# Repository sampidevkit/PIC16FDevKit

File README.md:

# PIC16F877A MICROCONTROLLER DEVELOPMENT KIT

## 1. Sơ Đồ Khối

## 2. Sơ Đồ Nguyên Lý

## 3. Vi Điều Khiển Chính PIC16F877A

## 4. Môi Trường Lập Trình, Trình Biên Dịch và Công Cụ Hỗ Trợ

### 4.1. Môi Trường Lập Trình MPLAB X IDE

### 4.2. Trình Biên Dịch MPLAB XC8

## 5. Mạch Nạp Tích Hợp

### 5.1. Nạp Chương Trình Mạch Nạp

### 5.2. Cập Nhật Chương Trình Mạch Nạp

### 5.3 Các Trạng Thái LED Lỗi

## 6. Hướng Dẫn Lập Trình Cơ Bản

## 7. Tài Liệu Kỹ Thuật:
* [PIC16F87XA Datasheet](https://ww1.microchip.com/downloads/aemDocuments/documents/MCU08/ProductDocuments/DataSheets/39582C.pdf).
* [PIC16F87XA Programming Specifications](https://ww1.microchip.com/downloads/en/DeviceDoc/39589C.pdf).

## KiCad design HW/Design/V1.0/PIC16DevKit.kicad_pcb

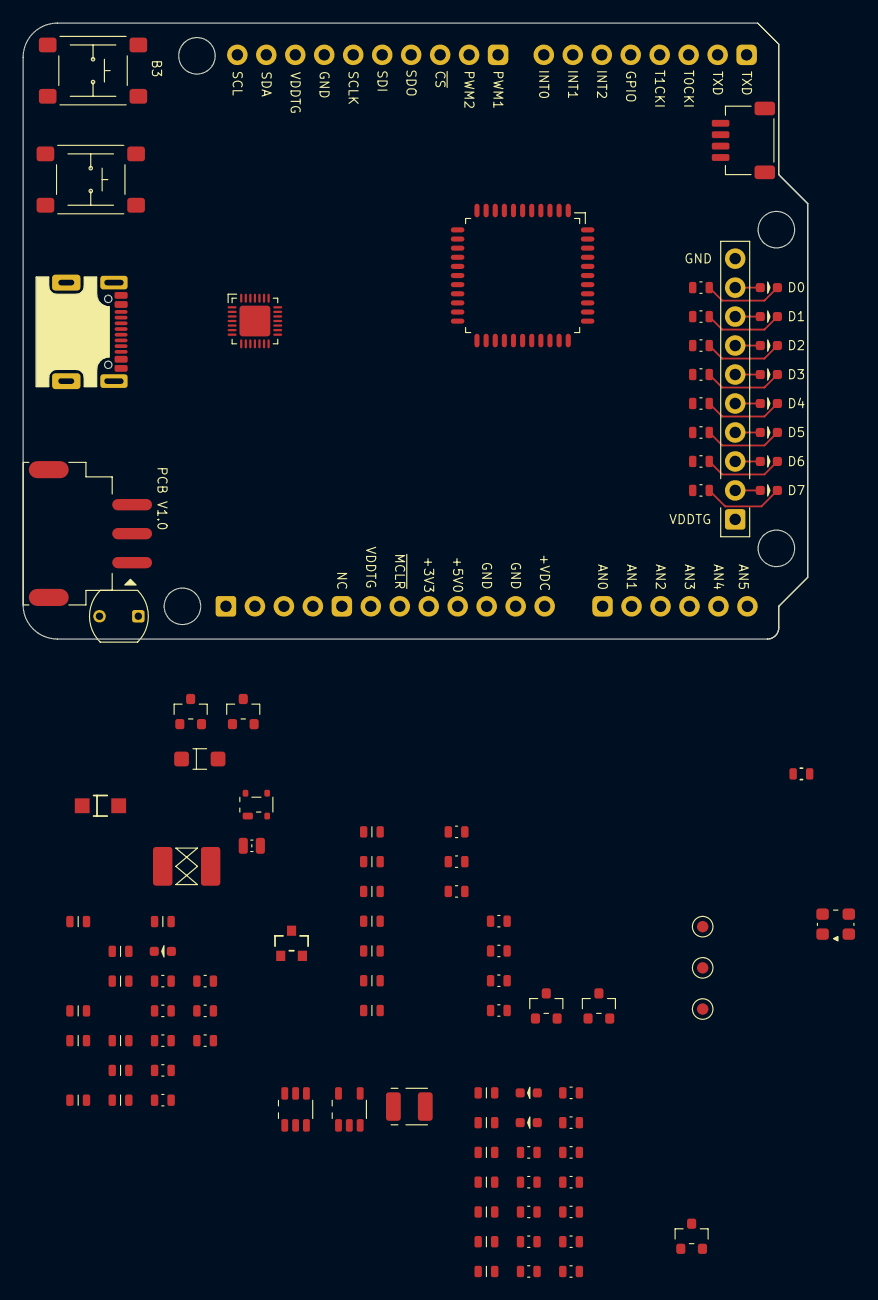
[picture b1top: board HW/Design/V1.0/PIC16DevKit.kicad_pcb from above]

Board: 4 copper layers, 68.8 x 54.0 mm, 99 parts (0 on the bottom side), 84 nets.

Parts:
BT301: FNC; SW6x6-G
BT401: UBT; SW6x6-G
C202, C207, C209, C211, C212, C218, C307, C404: 10uF; CAP0603
C205, C214, C402, C403: 22pF; CAP0603
C215, C216, C301, C302, C303, C304, C305, C401, C405, C406, C407: 100nF; CAP0603
C217: 220uF; CAP1411
C306: 470nF; CAP0603
D201: TVS 5V; SOT143B_NEXT
D202, D204: 200mA/0.2VF; SOD-123FL
D205: POWER; LED0603
D301: TGRD; LED0603
D302: BUSY; LED0603
D401: D7; LED0603
D402: D6; LED0603
D403: D5; LED0603
D404: D4; LED0603
D405: D3; LED0603
D406: D2; LED0603
D407: D1; LED0603
D408: D0; LED0603
F202: 500mA; FUSE1812
J201: USB C; USB4105
J401: EXP PORT; HDM1x10x2.54_TH
J402: QWIIC; HDM-1x4x1.0-RA
J403: For DS18B20; JST-XH2.54-3P-SMD-RA
L201: 10uH/100mA; IND0805
MD401: ARDUINO-UNO-R3
Q201, Q202: SI2301; SOT23
Q203: 2N3906; SOT23
Q301, Q401, Q402: SI2302; SOT23
R201, R202, R413, R414, R415, R416, R417: 5.1K; RES0603
R203, R204, R205: 100K; RES0603
R208: 191K; RES0603
R209, R303, R305, R401, R403: 10K; RES0603
R210, R405, R406, R407, R408, R409, R410, R411, R412: 1K; RES0603
R301, R302, R304, R306, R307, R308, R309, R310, R311, R312, R404: 330R; RES0603
R402: 10K; CDS-5MM
TP401: PGM/B3; TP1MM
TP402: PGC/B6; TP1MM
TP403: PGD/B7; TP1MM
U202: BOOST 12V; SOT-23-6_MCHP
U203: LDO 3.3V/300mA; SOT-23-5_MCHP
U301: AVRxxDU28; VQFN28-4x4-EP
U401: 20MHz; CDFN3225-4LD-PL-1
U402: PIC16F877A; TQFP44-10x10-P0.8

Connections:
+3.3V: C218.2, J402.2 (VDD), MD401.4 (+3V3), Q401.1 (G), Q402.1 (G), R415.2, R416.2, U203.5 (VOUT)
+5V: C205.1, C207.2, C215.1, C217.+, C304.1, C305.1, C307.1, L201.1, MD401.5 (+5V), MD401.P2 (+5V), Q201.2 (S), Q202.2 (S), Q203.2 (E), R205.1, R210.2, R303.2, R305.2, U202.5 (IN), U301.18 (VDD), U301.24 (VDD)
+VDDTG: C209.2, C211.2, C406.1, C407.1, J401.1, MD401.2 (IOREF), MD401.30 (AREF), Q202.3 (D), R403.1, R404.1, R413.2, R414.2, R417.2, U203.1 (VIN), U402.7 (VDD), U402.28 (VDD)
/POWER/USB_N: D201.3 (CH2), J201.A7 (DN1), J201.B7 (DN2), U301.7 (DM)
/POWER/USB_P: D201.2 (CH1), J201.A6 (DP1), J201.B6 (DP2), U301.8 (DP)
/POWER/V33_EN: U203.3 (EN), U301.12 (PD2/ACINP/AIN9)
/POWER/VPP_EN: U202.4 (EN), U301.21 (PF1/ANI16/XTAL32K2)
/POWER/~VTG_EN: C205.2, Q202.1 (G), R205.2, U301.20 (PF0/AIN15/XTAL32K1)
/PROGRAMMER/RXD0: R309.2, U402.1 (DT/RX/RC7), U402.44 (CK/TX/RC6)
/PROGRAMMER/RXD1: MD401.15 (D0/RXD), R310.2
/PROGRAMMER/SCL: MD401.32 (D15/SCL), Q401.3 (D), R308.2, R413.1, TP402.1, U301.1 (PA3/A1RX0/SCL/AIN1), U402.16 (PGC/RB6)
/PROGRAMMER/SDA: MD401.31 (D14/SDA), Q402.3 (D), R306.2, R414.1, TP403.1, U301.28 (PA2/A1TX0/SDA/AIN0), U402.17 (PGD/RB7)
/PROGRAMMER/TXD1: MD401.16 (D1/TXD), R312.2
/PROGRAMMER/UPDI: MD401.P4 (UPDI), U301.23 (PF7/UPDI)
/PROGRAMMER/~RESET: C303.2, MD401.P1 (~RESET), R305.1, U301.22 (PF6/~RESET)
/PROGRAMMER/~TG_MCLR: C302.1, MD401.3 (~MCLR), Q301.3 (D), R304.1, U402.18 (~MCLR/VPP)
/PROGRAMMER/~TG_PGM: BT401.1, BT401.2, C405.1, R307.2, R403.2, TP401.1, U402.11 (PGM/RB3)
AN0: MD401.9 (AN0), U402.19 (AN0/RA0)
AN1: MD401.10 (AN1), U402.20 (AN1/RA1)
AN2: MD401.11 (AN2), U402.21 (CVREF/VREF-/AN2/RA2)
AN3: MD401.12 (AN3), U402.22 (VREF+/AN3/RA3)
AN4: MD401.13 (AN4/SDA), U402.24 (~SS/C2OUT/AN4/RA5)
AN5: MD401.14 (AN5/SCL), U402.25 (RE0/~RD/AN5)
GND: BT301.3, BT301.4, BT401.3, BT401.4, C202.1, C207.1, C209.1, C211.1, C212.2, C215.2, C216.2, C217.-, C218.1, C301.2, C302.2, C303.1, C304.2, C305.2, C306.2, C307.2, C401.2, C402.1, C403.2, C404.1, C405.2, C406.2, C407.2, D201.1 (GND), D205.K, D301.K, D302.K, J201.A1B12 (GND), J201.B1A12 (GND), J201.S1, J201.S2, J201.S3, J201.S4, J401.10, J402.0 (EP), J402.1 (GND), J403.0 (EP), J403.1 (GND), MD401.6 (GND), MD401.7 (GND), MD401.29 (GND), MD401.P3 (GND), Q301.2 (S), R201.2, R202.1, R203.2, R204.2, R209.2, R401.2, R405.1, R406.1, R407.1, R408.1, R409.1, R410.1, R411.1, R412.1, U202.2 (GND), U203.2 (GND), U301.19 (GND), U301.25 (GND), U301.29 (EP), U401.2 (GND1), U401.4 (X2), U402.6 (VSS), U402.29 (VSS)
GPIO: MD401.19 (D4), U402.15 (RB5)
INT0: MD401.22 (D7), U402.8 (INT/RB0)
INT1: MD401.21 (D6), U402.9 (RB1)
INT2: MD401.20 (D5), U402.10 (RB2)
LED_BUSY: R302.2, U301.3 (PA5/MISO/A2RX0/AIN3)
LED_TGRDY: R301.2, U301.2 (PA4/MOSI/A2TX0/AIN2)
LIGHT: C401.1, R401.1, R402.1, U402.27 (RE2/~CS/AN7)
unnamed: D201.4 (CH3), F202.1, J201.A4B9 (VBUS), J201.B4A9 (VBUS)
unnamed: D205.A, R210.1
unnamed: D301.A, R301.1
unnamed: D302.A, R302.1
unnamed: D401.K, R405.2
unnamed: D402.K, R406.2
unnamed: D403.K, R407.2
unnamed: D404.K, R408.2
unnamed: D405.K, R409.2
unnamed: D406.K, R410.2
unnamed: D407.K, R411.2
unnamed: D408.K, R412.2
unnamed: J201.A5 (CC1), R202.2
unnamed: J201.B5 (CC2), R201.1
unnamed: J402.4 (SCL), Q401.2 (S), R415.1
unnamed: J402.3 (SDA), Q402.2 (S), R416.1
unnamed: C404.2, J403.3 (VDD), R402.2, R404.2
unnamed: Q201.1 (G), Q203.3 (C), R204.1
unnamed: D202.K, Q203.1 (B), R203.1
unnamed: C214.2, R208.2, R209.1, U202.3 (FB)
unnamed: D204.A, L201.2, U202.1 (SW)
unnamed: C216.1, U203.4 (NC/BP)
unnamed: R308.1, U301.26 (PA0/TX0/ASDA/XTALHF1)
unnamed: R306.1, U301.27 (PA1/RX0/ASCL/XTALHF2)
unnamed: R307.1, U301.4 (PA6/SCLK/AIN4)
unnamed: R311.1, U301.14 (PD4/AMOSI/A3TX0/AIN11)
unnamed: R309.1, U301.15 (PD5/AMISO/A3RX0/AIN12)
unnamed: R312.1, U301.16 (PD6/ASCLK/TX1/ACINP/AIN13)
unnamed: R310.1, U301.17 (PD7/RX1/AINN/AIN14)
unnamed: C306.1, U301.6 (VUSB)
unnamed: C403.1, U401.3 (GND2), U402.30 (OSC1/CLKI)
unnamed: C402.2, U401.1 (X1), U402.31 (OSC2/CLKO)
ONE_WIRE: J403.2 (DQ), R417.1, U402.26 (RE1/~WR/AN6)
PWM1: MD401.23 (D8), U402.36 (CCP1/RC2)
PWM2: MD401.24 (D9), U402.35 (T1OSI/CCP2/RC1)
RD0: D408.A, J401.9, U402.5 (RD7/PSP7)
RD1: D407.A, J401.8, U402.4 (RD6/PSP6)
RD2: D406.A, J401.7, U402.3 (RD5/PSP5)
RD3: D405.A, J401.6, U402.2 (RD4/PSP4)
RD4: D404.A, J401.5, U402.41 (RD3/PSP3)
RD5: D403.A, J401.4, U402.40 (RD2/PSP2)
RD6: D402.A, J401.3, U402.39 (RD1/PSP1)
RD7: D401.A, J401.2, U402.38 (RD0/PSP0)
SCLK: MD401.28 (D13/SCLK), U402.37 (SCK/SCL/RC3)
SDI: MD401.27 (D12/MISO), U402.42 (SDI/SDA/RC4)
SDO: MD401.26 (D11/MOSI), U402.43 (SDO/RC5)
T0CKI: MD401.17 (D2), U402.23 (C1OUT/T0CKI/RA4)
T1CKI: MD401.18 (D3), U402.32 (T1OSO/T1CKI/RC0)
TG_MCLR: Q301.1 (G), U301.13 (PD3/ACINN/AIN10)
VBUS: C202.2, D202.A, F202.2, Q201.3 (D)
VPP: C212.1, C214.1, D204.K, R208.1, R304.2
~BT_FNC: BT301.1, BT301.2, C301.1, R303.1, U301.5 (PA7/ACOUT/AIN5)
~CS: MD401.25 (D10/~SS), U402.14 (RB4)

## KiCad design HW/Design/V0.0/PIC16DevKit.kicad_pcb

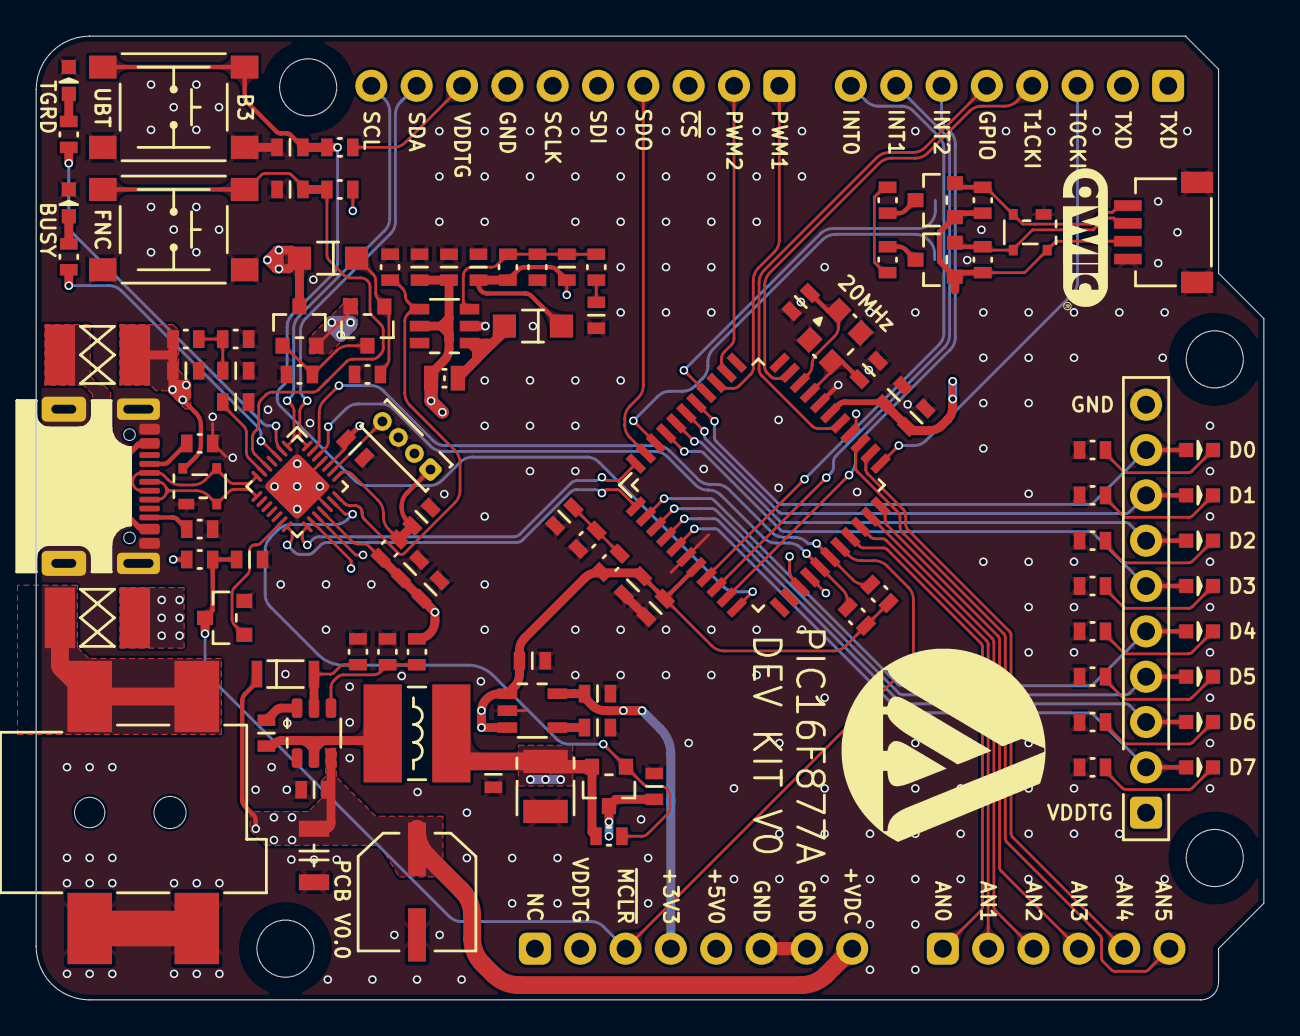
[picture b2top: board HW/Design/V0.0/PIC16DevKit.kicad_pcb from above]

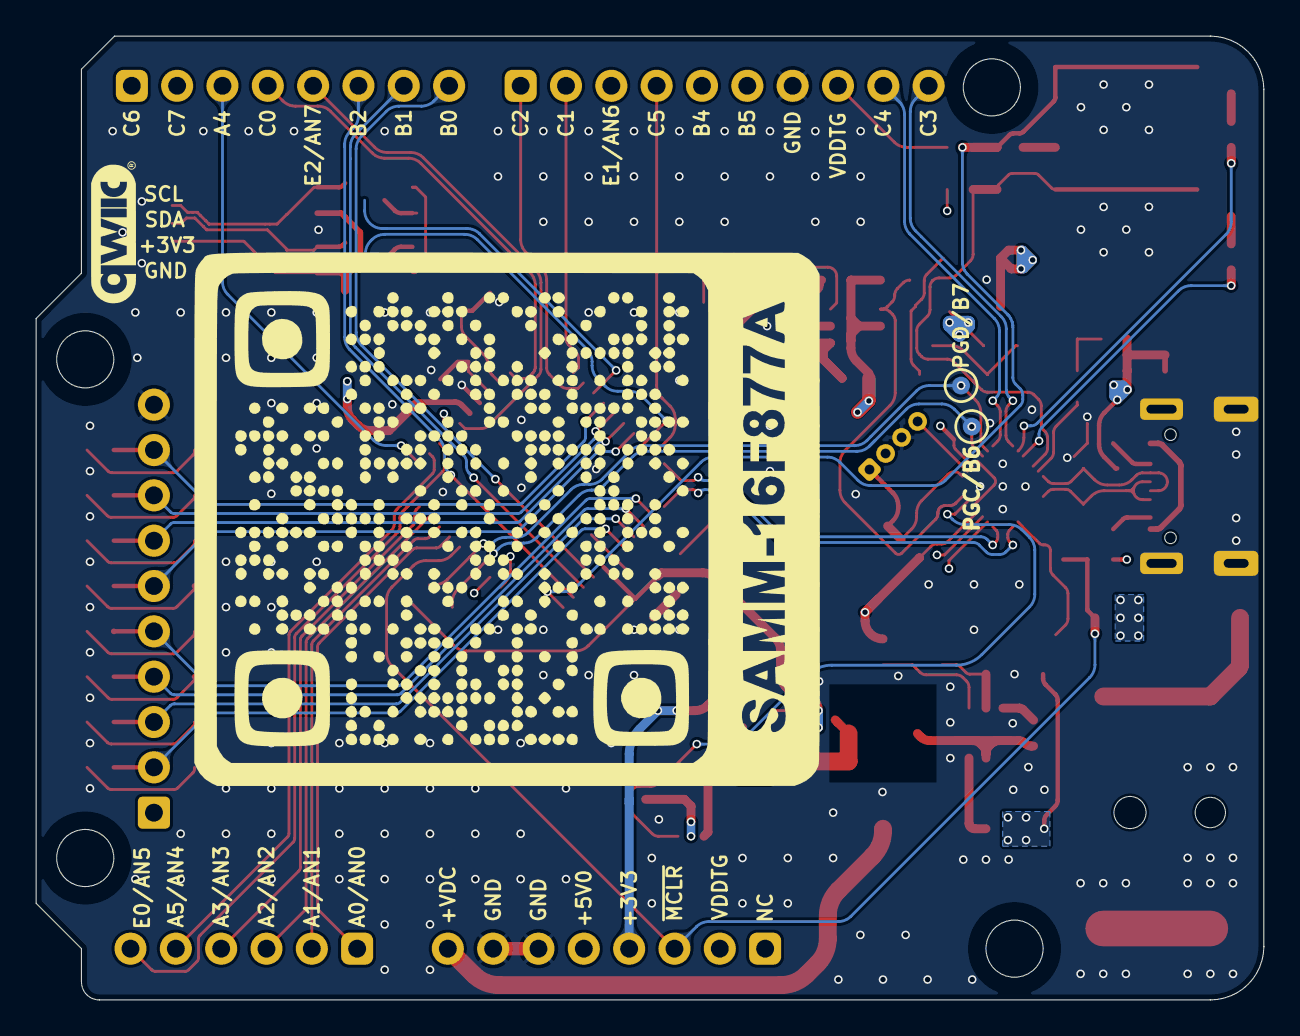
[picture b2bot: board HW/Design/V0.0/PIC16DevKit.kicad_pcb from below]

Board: 4 copper layers, 68.8 x 54.0 mm, 109 parts (2 on the bottom side), 84 nets.

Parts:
BT1: FNC; SW6x6-G
BT2: UBT; SW6x6-G
C1: 220uF; CAP_ELEC-6.6x6.6-DIA6.3
C2: 220uF; CAP1411
C3: 10uF/16V; CAP1206
C4, C5, C6, C14, C17, C18, C20, C22, C25, C26, C32, C37, C38, C39, C40, C41: 100nF; CAP0603
C7, C8, C9, C10, C11, C13, C19, C21, C27: 10uF; CAP0603
C12, C15, C16: 22pF; CAP0603
C23: 470nF; CAP0603
D1: 5V1; SOD80C-LL34
D2, D4: 200mA/0.2VF; SOD-123FL
D3, D5: TVS 5V; SOT143B_NEXT
D6: TGRD; LED0603
D7: BUSY; LED0603
D8: D0; LED0603
D9: D1; LED0603
D10: D2; LED0603
D11: D3; LED0603
D12: D4; LED0603
D13: D5; LED0603
D14: D6; LED0603
D15: D7; LED0603
F1: 1A; FUSE1812
F2: 500mA; FUSE1812
J1: 9V-12V; PJ-002AH-SMT
J2: USB C; USB4105
J3: EXP PORT; HDM1x10x2.54_TH
J4: SIL04; HD-1x4x1.27MM-TH
J5: QWIIC; HDM-1x4x1.0-RA
L1: 10uH/1.4A; IND5852
L2: 10uH/100mA; IND0805
MD1: ARDUINO-UNO-R3
Q1, Q3: SI2301; SOT23
Q4: 2N3906; SOT23
Q5, Q6, Q7: SI2302; SOT23
R1: 52.3K, 1%; RES0603
R2, R10, R36: 10K, 1%; RES0603
R3, R8, R9, R31: 100K; RES0603
R4, R18, R23, R26: 10K; RES0603
R5: 191K, 1%; RES0603
R6, R7, R19, R21, R22, R27, R28, R30, R32, R35: 5.1K, 1%; RES0603
R11, R12, R13, R14, R15, R16, R17, R20, R24, R25, R29: 330R; RES0603
R33, R34: 47K, 1%; RES0603
TP1: PGC/B6; TP1MM
TP2: PGD/B7; TP1MM
U1: LDO 3.3V/300mA; SOT-23-5_MCHP
U2: MT1470; SOT-23-6_MCHP
U3: MT3608; SOT-23-6_MCHP
U4: PIC16F877A; TQFP44-10x10-P0.8
U5: AVRxxDU28; VQFN28-4x4-EP
U10: 20MHz; CDFN3225-4LD-PL-1

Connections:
+3.3V: C8.1, D5.4 (CH3), J5.2 (VDD), MD1.4 (+3V3), Q6.1 (G), Q7.1 (G), R28.1, R30.1, U1.5 (VOUT)
+5V: C2.+, C6.1, C13.1, C14.1, C25.1, C26.1, C27.1, J4.2, L1.2, L2.1, MD1.5 (+5V), Q1.2 (S), Q3.2 (S), Q4.2 (E), R1.1, R4.1, R23.1, R26.1, U3.5 (IN), U5.18 (VDD), U5.24 (VDD)
+VDDTG: C7.1, C9.1, C18.1, C19.1, C20.1, C21.1, J3.1, MD1.2 (IOREF), MD1.30 (AREF), Q1.3 (D), R18.1, R19.1, R21.1, R22.1, R27.1, R34.1, U1.1 (VIN), U1.3 (EN), U4.7 (VDD), U4.28 (VDD)
/POWER/USB_N: D3.3 (CH2), J2.A7 (DN1), J2.B7 (DN2), U5.7 (DM)
/POWER/USB_P: D3.2 (CH1), J2.A6 (DP1), J2.B6 (DP2), U5.8 (DP)
/POWER/VBUS_DIV: C39.1, R32.1, R33.2, U5.9 (PC3/ACINP/AIN6)
/POWER/VDDTG_DIV: C40.1, R34.2, R35.1, U5.11 (PD1/AIN8)
/POWER/VPP_DIV: C41.1, R36.2, U5.10 (PD0/ACINN/AIN7)
/POWER/VPP_EN: R31.1, U3.4 (EN), U5.21 (PF1/ANI16/XTAL32K2)
/POWER/~VTG_EN: Q1.1 (G), R4.2, U5.20 (PF0/AIN15/XTAL32K1)
/PROGRAMMER/LED_BUSY: R25.1, U5.3 (PA5/MISO/A2RX0/AIN3)
/PROGRAMMER/LED_TGRDY: R24.1, U5.2 (PA4/MOSI/A2TX0/AIN2)
/PROGRAMMER/PG_UPDI: J4.4, U5.23 (PF7/UPDI)
/PROGRAMMER/RXD0: U4.44 (CK/TX/RC6), U5.15 (PD5/AMISO/A3RX0/AIN12)
/PROGRAMMER/RXD1: MD1.16 (D1/TXD), U5.17 (PD7/RX1/AINN/AIN14)
/PROGRAMMER/SCL: MD1.32 (D15/SCL), Q6.3 (D), R22.2, U4.37 (SCK/SCL/RC3), U5.1 (PA3/A1RX0/SCL/AIN1)
/PROGRAMMER/SDA: MD1.31 (D14/SDA), Q7.3 (D), R21.2, U4.42 (SDI/SDA/RC4), U5.28 (PA2/A1TX0/SDA/AIN0)
/PROGRAMMER/TG_MCLR: Q5.1 (G), U5.13 (PD3/ACINN/AIN10)
/PROGRAMMER/TG_PGC: R19.2, TP1.1, U4.16 (PGC/RB6), U5.26 (PA0/TX0/ASDA/XTALHF1)
/PROGRAMMER/TG_PGD: R27.2, TP2.1, U4.17 (PGD/RB7), U5.27 (PA1/RX0/ASCL/XTALHF2)
/PROGRAMMER/TXD0: U4.1 (DT/RX/RC7), U5.14 (PD4/AMOSI/A3TX0/AIN11)
/PROGRAMMER/TXD1: MD1.15 (D0/RXD), U5.16 (PD6/ASCLK/TX1/ACINP/AIN13)
/PROGRAMMER/~BT_FNC: BT1.1, BT1.2, C22.1, R23.2, U5.5 (PA7/ACOUT/AIN5)
/PROGRAMMER/~PG_RESET: C32.2, J4.1, R26.2, U5.22 (PF6/~RESET)
/PROGRAMMER/~TG_MCLR: C37.1, MD1.3 (RESET), Q5.3 (D), R29.2, U4.18 (~MCLR/VPP)
/TARGET MCU/AN0: MD1.9 (AN0), U4.19 (AN0/RA0)
/TARGET MCU/AN1: MD1.10 (AN1), U4.20 (AN1/RA1)
/TARGET MCU/AN2: MD1.11 (AN2), U4.21 (CVREF/VREF-/AN2/RA2)
/TARGET MCU/AN3: MD1.12 (AN3), U4.22 (VREF+/AN3/RA3)
/TARGET MCU/AN4: MD1.13 (AN4/SDA), U4.24 (~SS/C2OUT/AN4/RA5)
/TARGET MCU/AN5: MD1.14 (AN5/SCL), U4.25 (RE0/~RD/AN5)
/TARGET MCU/GPIO: MD1.19 (D4), U4.27 (RE2/~CS/AN7)
/TARGET MCU/INT0: MD1.22 (D7), U4.8 (INT/RB0)
/TARGET MCU/INT1: MD1.21 (D6), U4.9 (RB1)
/TARGET MCU/INT2: MD1.20 (D5), U4.10 (RB2)
/TARGET MCU/PWM1: MD1.23 (D8), U4.36 (CCP1/RC2)
/TARGET MCU/PWM2: MD1.24 (D9), U4.35 (T1OSI/CCP2/RC1)
/TARGET MCU/RD0: D8.A, J3.9, U4.38 (RD0/PSP0)
/TARGET MCU/RD1: D9.A, J3.8, U4.39 (RD1/PSP1)
/TARGET MCU/RD2: D10.A, J3.7, U4.40 (RD2/PSP2)
/TARGET MCU/RD3: D11.A, J3.6, U4.41 (RD3/PSP3)
/TARGET MCU/RD4: D12.A, J3.5, U4.2 (RD4/PSP4)
/TARGET MCU/RD5: D13.A, J3.4, U4.3 (RD5/PSP5)
/TARGET MCU/RD6: D14.A, J3.3, U4.4 (RD6/PSP6)
/TARGET MCU/RD7: D15.A, J3.2, U4.5 (RD7/PSP7)
/TARGET MCU/SCLK: MD1.28 (D13/SCLK), U4.15 (RB5)
/TARGET MCU/SDI: MD1.27 (D12/MISO), U4.14 (RB4)
/TARGET MCU/SDO: MD1.26 (D11/MOSI), U4.43 (SDO/RC5)
/TARGET MCU/T0CKI: MD1.17 (D2), U4.23 (C1OUT/T0CKI/RA4)
/TARGET MCU/T1CKI: MD1.18 (D3), U4.32 (T1OSO/T1CKI/RC0)
/TARGET MCU/~CS: MD1.25 (D10/~SS), U4.26 (RE1/~WR/AN6)
/TARGET MCU/~UBT: BT2.1, BT2.2, C17.2, R18.2, U4.11 (PGM/RB3)
GND: BT1.3, BT1.4, BT2.3, BT2.4, C1.-, C2.-, C3.2, C4.2, C6.2, C7.2, C8.2, C9.2, C10.2, C11.2, C13.2, C14.2, C15.1, C16.1, C17.1, C18.2, C19.2, C20.2, C21.2, C22.2, C23.2, C25.2, C26.2, C27.2, C32.1, C37.2, C38.2, C39.2, C40.2, C41.2, D3.1 (GND), D5.1 (GND), D6.K, D7.K, J1.2, J1.3, J2.A1B12 (GND), J2.B1A12 (GND), J2.S1, J2.S2, J2.S3, J2.S4, J3.10, J4.3, J5.0 (EP), J5.1 (GND), MD1.6 (GND), MD1.7 (GND), MD1.29 (GND), Q5.2 (S), R2.2, R3.2, R6.2, R7.2, R8.2, R9.2, R10.2, R11.1, R12.1, R13.1, R14.1, R15.1, R16.1, R17.1, R20.1, R31.2, R32.2, R35.2, U1.2 (GND), U2.1 (GND), U3.2 (GND), U4.6 (VSS), U4.29 (VSS), U5.19 (GND), U5.25 (GND), U5.29 (EP), U10.2 (GND1), U10.4 (X2)
unnamed: D5.2 (CH1), J5.4 (SCL), Q6.2 (S), R28.2
unnamed: D5.3 (CH2), J5.3 (SDA), Q7.2 (S), R30.2
unnamed: D6.A, R24.2
unnamed: D7.A, R25.2
unnamed: D8.K, R20.2
unnamed: D9.K, R17.2
unnamed: D10.K, R16.2
unnamed: D11.K, R15.2
unnamed: D12.K, R14.2
unnamed: D13.K, R13.2
unnamed: D14.K, R12.2
unnamed: D15.K, R11.2
unnamed: F1.1, J1.1
unnamed: F2.1, J2.A4B9 (VBUS), J2.B4A9 (VBUS)
unnamed: J2.A5 (CC1), R7.1
unnamed: J2.B5 (CC2), R6.1
unnamed: Q3.1 (G), Q4.3 (C), R9.1
unnamed: D4.K, Q4.1 (B), R8.1
unnamed: C38.1, U1.4 (NC/BP)
unnamed: C5.2, U2.6 (BS)
unnamed: D1.A, R3.1, U2.5 (EN)
unnamed: R1.2, R2.1, U2.4 (FB)
unnamed: C5.1, L1.1, U2.2 (SW)
unnamed: C12.2, R5.2, R10.1, R36.1, U3.3 (FB)
unnamed: D2.A, L2.2, U3.1 (SW)
unnamed: C23.1, U5.6 (VUSB)
unnamed: C15.2, U4.30 (OSC1/CLKI), U10.3 (GND2)
unnamed: C16.2, U4.31 (OSC2/CLKO), U10.1 (X1)
VBUS: C10.1, D3.4 (CH3), D4.A, F2.2, Q3.3 (D), R33.1
VDC: C1.+, C3.1, C4.1, D1.K, F1.2, MD1.8 (VIN), U2.3 (IN)
VPP: C11.1, C12.1, D2.K, R5.1, R29.1

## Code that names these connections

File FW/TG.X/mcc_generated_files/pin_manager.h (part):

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#define RA0_SetHigh()            do { LATAbits.LATA0 = 1; } while(0)
#define RA0_SetLow()             do { LATAbits.LATA0 = 0; } while(0)
#define RA0_Toggle()             do { LATAbits.LATA0 = ~LATAbits.LATA0; } while(0)
#define RA0_GetValue()              PORTAbits.RA0
#define RA0_SetDigitalInput()    do { TRISAbits.TRISA0 = 1; } while(0)
#define RA0_SetDigitalOutput()   do { TRISAbits.TRISA0 = 0; } while(0)
#define RA0_SetPullup()             do { WPUAbits.WPUA0 = 1; } while(0)
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#define RA1_SetHigh()            do { LATAbits.LATA1 = 1; } while(0)
#define RA1_SetLow()             do { LATAbits.LATA1 = 0; } while(0)
#define RA1_Toggle()             do { LATAbits.LATA1 = ~LATAbits.LATA1; } while(0)
#define RA1_GetValue()              PORTAbits.RA1
#define RA1_SetDigitalInput()    do { TRISAbits.TRISA1 = 1; } while(0)
#define RA1_SetDigitalOutput()   do { TRISAbits.TRISA1 = 0; } while(0)
#define RA1_SetPullup()             do { WPUAbits.WPUA1 = 1; } while(0)
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// get/set ULED aliases
#define ULED_TRIS                 TRISAbits.TRISA2
#define ULED_LAT                  LATAbits.LATA2
#define ULED_PORT                 PORTAbits.RA2
#define ULED_WPU                  WPUAbits.WPUA2
#define ULED_OD                   ODCONAbits.ODA2
#define ULED_ANS                  ANSELAbits.ANSA2
#define ULED_SetHigh()            do { LATAbits.LATA2 = 1; } while(0)
#define ULED_SetLow()             do { LATAbits.LATA2 = 0; } while(0)
#define ULED_Toggle()             do { LATAbits.LATA2 = ~LATAbits.LATA2; } while(0)
#define ULED_GetValue()           PORTAbits.RA2
#define ULED_SetDigitalInput()    do { TRISAbits.TRISA2 = 1; } while(0)
#define ULED_SetDigitalOutput()   do { TRISAbits.TRISA2 = 0; } while(0)
#define ULED_SetPullup()          do { WPUAbits.WPUA2 = 1; } while(0)
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#define RA4_SetHigh()            do { LATAbits.LATA4 = 1; } while(0)
#define RA4_SetLow()             do { LATAbits.LATA4 = 0; } while(0)
#define RA4_Toggle()             do { LATAbits.LATA4 = ~LATAbits.LATA4; } while(0)
#define RA4_GetValue()              PORTAbits.RA4
#define RA4_SetDigitalInput()    do { TRISAbits.TRISA4 = 1; } while(0)
#define RA4_SetDigitalOutput()   do { TRISAbits.TRISA4 = 0; } while(0)
#define RA4_SetPullup()             do { WPUAbits.WPUA4 = 1; } while(0)
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#define RA5_SetHigh()            do { LATAbits.LATA5 = 1; } while(0)
#define RA5_SetLow()             do { LATAbits.LATA5 = 0; } while(0)
#define RA5_Toggle()             do { LATAbits.LATA5 = ~LATAbits.LATA5; } while(0)
#define RA5_GetValue()              PORTAbits.RA5
#define RA5_SetDigitalInput()    do { TRISAbits.TRISA5 = 1; } while(0)
#define RA5_SetDigitalOutput()   do { TRISAbits.TRISA5 = 0; } while(0)
#define RA5_SetPullup()             do { WPUAbits.WPUA5 = 1; } while(0)
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// get/set SCK aliases
#define SCK_TRIS                 TRISBbits.TRISB4
#define SCK_LAT                  LATBbits.LATB4
#define SCK_PORT                 PORTBbits.RB4
#define SCK_WPU                  WPUBbits.WPUB4
#define SCK_OD                   ODCONBbits.ODB4
#define SCK_ANS                  ANSELBbits.ANSB4
#define SCK_SetHigh()            do { LATBbits.LATB4 = 1; } while(0)
#define SCK_SetLow()             do { LATBbits.LATB4 = 0; } while(0)
#define SCK_Toggle()             do { LATBbits.LATB4 = ~LATBbits.LATB4; } while(0)
#define SCK_GetValue()           PORTBbits.RB4
#define SCK_SetDigitalInput()    do { TRISBbits.TRISB4 = 1; } while(0)
#define SCK_SetDigitalOutput()   do { TRISBbits.TRISB4 = 0; } while(0)
#define SCK_SetPullup()          do { WPUBbits.WPUB4 = 1; } while(0)
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#define RB5_SetHigh()            do { LATBbits.LATB5 = 1; } while(0)
#define RB5_SetLow()             do { LATBbits.LATB5 = 0; } while(0)
#define RB5_Toggle()             do { LATBbits.LATB5 = ~LATBbits.LATB5; } while(0)
#define RB5_GetValue()              PORTBbits.RB5
#define RB5_SetDigitalInput()    do { TRISBbits.TRISB5 = 1; } while(0)
#define RB5_SetDigitalOutput()   do { TRISBbits.TRISB5 = 0; } while(0)
#define RB5_SetPullup()             do { WPUBbits.WPUB5 = 1; } while(0)
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#define RB6_SetHigh()            do { LATBbits.LATB6 = 1; } while(0)
#define RB6_SetLow()             do { LATBbits.LATB6 = 0; } while(0)
#define RB6_Toggle()             do { LATBbits.LATB6 = ~LATBbits.LATB6; } while(0)
#define RB6_GetValue()              PORTBbits.RB6
#define RB6_SetDigitalInput()    do { TRISBbits.TRISB6 = 1; } while(0)
#define RB6_SetDigitalOutput()   do { TRISBbits.TRISB6 = 0; } while(0)
#define RB6_SetPullup()             do { WPUBbits.WPUB6 = 1; } while(0)
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// get/set GPIO1 aliases
#define GPIO1_TRIS                 TRISBbits.TRISB7
#define GPIO1_LAT                  LATBbits.LATB7
#define GPIO1_PORT                 PORTBbits.RB7
#define GPIO1_WPU                  WPUBbits.WPUB7
#define GPIO1_OD                   ODCONBbits.ODB7
#define GPIO1_ANS                  ANSELBbits.ANSB7
#define GPIO1_SetHigh()            do { LATBbits.LATB7 = 1; } while(0)
#define GPIO1_SetLow()             do { LATBbits.LATB7 = 0; } while(0)
#define GPIO1_Toggle()             do { LATBbits.LATB7 = ~LATBbits.LATB7; } while(0)
#define GPIO1_GetValue()           PORTBbits.RB7
#define GPIO1_SetDigitalInput()    do { TRISBbits.TRISB7 = 1; } while(0)
#define GPIO1_SetDigitalOutput()   do { TRISBbits.TRISB7 = 0; } while(0)
#define GPIO1_SetPullup()          do { WPUBbits.WPUB7 = 1; } while(0)
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// get/set NCS aliases
#define NCS_TRIS                 TRISCbits.TRISC0
#define NCS_LAT                  LATCbits.LATC0
#define NCS_PORT                 PORTCbits.RC0
#define NCS_WPU                  WPUCbits.WPUC0
#define NCS_OD                   ODCONCbits.ODC0
#define NCS_ANS                  ANSELCbits.ANSC0
#define NCS_SetHigh()            do { LATCbits.LATC0 = 1; } while(0)
#define NCS_SetLow()             do { LATCbits.LATC0 = 0; } while(0)
#define NCS_Toggle()             do { LATCbits.LATC0 = ~LATCbits.LATC0; } while(0)
#define NCS_GetValue()           PORTCbits.RC0
#define NCS_SetDigitalInput()    do { TRISCbits.TRISC0 = 1; } while(0)
#define NCS_SetDigitalOutput()   do { TRISCbits.TRISC0 = 0; } while(0)
#define NCS_SetPullup()          do { WPUCbits.WPUC0 = 1; } while(0)
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// get/set SDO aliases
#define SDO_TRIS                 TRISCbits.TRISC1
#define SDO_LAT                  LATCbits.LATC1
#define SDO_PORT                 PORTCbits.RC1
#define SDO_WPU                  WPUCbits.WPUC1
#define SDO_OD                   ODCONCbits.ODC1
#define SDO_ANS                  ANSELCbits.ANSC1
#define SDO_SetHigh()            do { LATCbits.LATC1 = 1; } while(0)
#define SDO_SetLow()             do { LATCbits.LATC1 = 0; } while(0)
#define SDO_Toggle()             do { LATCbits.LATC1 = ~LATCbits.LATC1; } while(0)
#define SDO_GetValue()           PORTCbits.RC1
#define SDO_SetDigitalInput()    do { TRISCbits.TRISC1 = 1; } while(0)
#define SDO_SetDigitalOutput()   do { TRISCbits.TRISC1 = 0; } while(0)
#define SDO_SetPullup()          do { WPUCbits.WPUC1 = 1; } while(0)
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// get/set SDI aliases
#define SDI_TRIS                 TRISCbits.TRISC2
#define SDI_LAT                  LATCbits.LATC2
#define SDI_PORT                 PORTCbits.RC2
#define SDI_WPU                  WPUCbits.WPUC2
#define SDI_OD                   ODCONCbits.ODC2
#define SDI_ANS                  ANSELCbits.ANSC2
#define SDI_SetHigh()            do { LATCbits.LATC2 = 1; } while(0)
#define SDI_SetLow()             do { LATCbits.LATC2 = 0; } while(0)
#define SDI_Toggle()             do { LATCbits.LATC2 = ~LATCbits.LATC2; } while(0)
#define SDI_GetValue()           PORTCbits.RC2
#define SDI_SetDigitalInput()    do { TRISCbits.TRISC2 = 1; } while(0)
#define SDI_SetDigitalOutput()   do { TRISCbits.TRISC2 = 0; } while(0)
#define SDI_SetPullup()          do { WPUCbits.WPUC2 = 1; } while(0)
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// get/set SAN0 aliases
#define SAN0_TRIS                 TRISCbits.TRISC3
#define SAN0_LAT                  LATCbits.LATC3
#define SAN0_PORT                 PORTCbits.RC3
#define SAN0_WPU                  WPUCbits.WPUC3
#define SAN0_OD                   ODCONCbits.ODC3
#define SAN0_ANS                  ANSELCbits.ANSC3
#define SAN0_SetHigh()            do { LATCbits.LATC3 = 1; } while(0)
#define SAN0_SetLow()             do { LATCbits.LATC3 = 0; } while(0)
#define SAN0_Toggle()             do { LATCbits.LATC3 = ~LATCbits.LATC3; } while(0)
#define SAN0_GetValue()           PORTCbits.RC3
#define SAN0_SetDigitalInput()    do { TRISCbits.TRISC3 = 1; } while(0)
#define SAN0_SetDigitalOutput()   do { TRISCbits.TRISC3 = 0; } while(0)
#define SAN0_SetPullup()          do { WPUCbits.WPUC3 = 1; } while(0)
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// get/set GPIO3 aliases
#define GPIO3_TRIS                 TRISCbits.TRISC4
#define GPIO3_LAT                  LATCbits.LATC4
#define GPIO3_PORT                 PORTCbits.RC4
#define GPIO3_WPU                  WPUCbits.WPUC4
#define GPIO3_OD                   ODCONCbits.ODC4
#define GPIO3_SetHigh()            do { LATCbits.LATC4 = 1; } while(0)
#define GPIO3_SetLow()             do { LATCbits.LATC4 = 0; } while(0)
#define GPIO3_Toggle()             do { LATCbits.LATC4 = ~LATCbits.LATC4; } while(0)
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
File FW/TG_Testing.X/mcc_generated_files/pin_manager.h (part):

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// get/set BLED aliases
#define BLED_TRIS                 TRISAbits.TRISA1
#define BLED_LAT                  LATAbits.LATA1
#define BLED_PORT                 PORTAbits.RA1
#define BLED_WPU                  WPUAbits.WPUA1
#define BLED_OD                   ODCONAbits.ODCA1
#define BLED_ANS                  ANSELAbits.ANSA1
#define BLED_SetHigh()            do { LATAbits.LATA1 = 1; } while(0)
#define BLED_SetLow()             do { LATAbits.LATA1 = 0; } while(0)
#define BLED_Toggle()             do { LATAbits.LATA1 = ~LATAbits.LATA1; } while(0)
#define BLED_GetValue()           PORTAbits.RA1
#define BLED_SetDigitalInput()    do { TRISAbits.TRISA1 = 1; } while(0)
#define BLED_SetDigitalOutput()   do { TRISAbits.TRISA1 = 0; } while(0)
#define BLED_SetPullup()          do { WPUAbits.WPUA1 = 1; } while(0)
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// get/set RTC_INT aliases
#define RTC_INT_TRIS                 TRISAbits.TRISA3
#define RTC_INT_LAT                  LATAbits.LATA3
#define RTC_INT_PORT                 PORTAbits.RA3
#define RTC_INT_WPU                  WPUAbits.WPUA3
#define RTC_INT_OD                   ODCONAbits.ODCA3
#define RTC_INT_ANS                  ANSELAbits.ANSA3
#define RTC_INT_SetHigh()            do { LATAbits.LATA3 = 1; } while(0)
#define RTC_INT_SetLow()             do { LATAbits.LATA3 = 0; } while(0)
#define RTC_INT_Toggle()             do { LATAbits.LATA3 = ~LATAbits.LATA3; } while(0)
#define RTC_INT_GetValue()           PORTAbits.RA3
#define RTC_INT_SetDigitalInput()    do { TRISAbits.TRISA3 = 1; } while(0)
#define RTC_INT_SetDigitalOutput()   do { TRISAbits.TRISA3 = 0; } while(0)
#define RTC_INT_SetPullup()          do { WPUAbits.WPUA3 = 1; } while(0)
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// get/set FLASH_nCS aliases
#define FLASH_nCS_TRIS                 TRISBbits.TRISB0
#define FLASH_nCS_LAT                  LATBbits.LATB0
#define FLASH_nCS_PORT                 PORTBbits.RB0
#define FLASH_nCS_WPU                  WPUBbits.WPUB0
#define FLASH_nCS_OD                   ODCONBbits.ODCB0
#define FLASH_nCS_ANS                  ANSELBbits.ANSB0
#define FLASH_nCS_SetHigh()            do { LATBbits.LATB0 = 1; } while(0)
#define FLASH_nCS_SetLow()             do { LATBbits.LATB0 = 0; } while(0)
#define FLASH_nCS_Toggle()             do { LATBbits.LATB0 = ~LATBbits.LATB0; } while(0)
#define FLASH_nCS_GetValue()           PORTBbits.RB0
#define FLASH_nCS_SetDigitalInput()    do { TRISBbits.TRISB0 = 1; } while(0)
#define FLASH_nCS_SetDigitalOutput()   do { TRISBbits.TRISB0 = 0; } while(0)
#define FLASH_nCS_SetPullup()          do { WPUBbits.WPUB0 = 1; } while(0)
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#define RB3_SetHigh()            do { LATBbits.LATB3 = 1; } while(0)
#define RB3_SetLow()             do { LATBbits.LATB3 = 0; } while(0)
#define RB3_Toggle()             do { LATBbits.LATB3 = ~LATBbits.LATB3; } while(0)
#define RB3_GetValue()              PORTBbits.RB3
#define RB3_SetDigitalInput()    do { TRISBbits.TRISB3 = 1; } while(0)
#define RB3_SetDigitalOutput()   do { TRISBbits.TRISB3 = 0; } while(0)
#define RB3_SetPullup()             do { WPUBbits.WPUB3 = 1; } while(0)
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#define RB4_SetHigh()            do { LATBbits.LATB4 = 1; } while(0)
#define RB4_SetLow()             do { LATBbits.LATB4 = 0; } while(0)
#define RB4_Toggle()             do { LATBbits.LATB4 = ~LATBbits.LATB4; } while(0)
#define RB4_GetValue()              PORTBbits.RB4
#define RB4_SetDigitalInput()    do { TRISBbits.TRISB4 = 1; } while(0)
#define RB4_SetDigitalOutput()   do { TRISBbits.TRISB4 = 0; } while(0)
#define RB4_SetPullup()             do { WPUBbits.WPUB4 = 1; } while(0)
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#define RB5_SetHigh()            do { LATBbits.LATB5 = 1; } while(0)
#define RB5_SetLow()             do { LATBbits.LATB5 = 0; } while(0)
#define RB5_Toggle()             do { LATBbits.LATB5 = ~LATBbits.LATB5; } while(0)
#define RB5_GetValue()              PORTBbits.RB5
#define RB5_SetDigitalInput()    do { TRISBbits.TRISB5 = 1; } while(0)
#define RB5_SetDigitalOutput()   do { TRISBbits.TRISB5 = 0; } while(0)
#define RB5_SetPullup()             do { WPUBbits.WPUB5 = 1; } while(0)
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#define RB6_SetHigh()            do { LATBbits.LATB6 = 1; } while(0)
#define RB6_SetLow()             do { LATBbits.LATB6 = 0; } while(0)
#define RB6_Toggle()             do { LATBbits.LATB6 = ~LATBbits.LATB6; } while(0)
#define RB6_GetValue()              PORTBbits.RB6
#define RB6_SetDigitalInput()    do { TRISBbits.TRISB6 = 1; } while(0)
#define RB6_SetDigitalOutput()   do { TRISBbits.TRISB6 = 0; } while(0)
#define RB6_SetPullup()             do { WPUBbits.WPUB6 = 1; } while(0)
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#define RB7_SetHigh()            do { LATBbits.LATB7 = 1; } while(0)
#define RB7_SetLow()             do { LATBbits.LATB7 = 0; } while(0)
#define RB7_Toggle()             do { LATBbits.LATB7 = ~LATBbits.LATB7; } while(0)
#define RB7_GetValue()              PORTBbits.RB7
#define RB7_SetDigitalInput()    do { TRISBbits.TRISB7 = 1; } while(0)
#define RB7_SetDigitalOutput()   do { TRISBbits.TRISB7 = 0; } while(0)
#define RB7_SetPullup()             do { WPUBbits.WPUB7 = 1; } while(0)
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// get/set VDDSS_nEN aliases
#define VDDSS_nEN_TRIS                 TRISDbits.TRISD0
#define VDDSS_nEN_LAT                  LATDbits.LATD0
#define VDDSS_nEN_PORT                 PORTDbits.RD0
#define VDDSS_nEN_WPU                  WPUDbits.WPUD0
#define VDDSS_nEN_OD                   ODCONDbits.ODCD0
#define VDDSS_nEN_ANS                  ANSELDbits.ANSD0
#define VDDSS_nEN_SetHigh()            do { LATDbits.LATD0 = 1; } while(0)
#define VDDSS_nEN_SetLow()             do { LATDbits.LATD0 = 0; } while(0)
#define VDDSS_nEN_Toggle()             do { LATDbits.LATD0 = ~LATDbits.LATD0; } while(0)
#define VDDSS_nEN_GetValue()           PORTDbits.RD0
#define VDDSS_nEN_SetDigitalInput()    do { TRISDbits.TRISD0 = 1; } while(0)
#define VDDSS_nEN_SetDigitalOutput()   do { TRISDbits.TRISD0 = 0; } while(0)
#define VDDSS_nEN_SetPullup()          do { WPUDbits.WPUD0 = 1; } while(0)
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// get/set TEMP aliases
#define TEMP_TRIS                 TRISDbits.TRISD1
#define TEMP_LAT                  LATDbits.LATD1
#define TEMP_PORT                 PORTDbits.RD1
#define TEMP_WPU                  WPUDbits.WPUD1
#define TEMP_OD                   ODCONDbits.ODCD1
#define TEMP_ANS                  ANSELDbits.ANSD1
#define TEMP_SetHigh()            do { LATDbits.LATD1 = 1; } while(0)
#define TEMP_SetLow()             do { LATDbits.LATD1 = 0; } while(0)
#define TEMP_Toggle()             do { LATDbits.LATD1 = ~LATDbits.LATD1; } while(0)
#define TEMP_GetValue()           PORTDbits.RD1
#define TEMP_SetDigitalInput()    do { TRISDbits.TRISD1 = 1; } while(0)
#define TEMP_SetDigitalOutput()   do { TRISDbits.TRISD1 = 0; } while(0)
#define TEMP_SetPullup()          do { WPUDbits.WPUD1 = 1; } while(0)
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// get/set UBT aliases
#define UBT_TRIS                 TRISDbits.TRISD3
#define UBT_LAT                  LATDbits.LATD3
#define UBT_PORT                 PORTDbits.RD3
#define UBT_WPU                  WPUDbits.WPUD3
#define UBT_OD                   ODCONDbits.ODCD3
#define UBT_ANS                  ANSELDbits.ANSD3
#define UBT_SetHigh()            do { LATDbits.LATD3 = 1; } while(0)
#define UBT_SetLow()             do { LATDbits.LATD3 = 0; } while(0)
#define UBT_Toggle()             do { LATDbits.LATD3 = ~LATDbits.LATD3; } while(0)
#define UBT_GetValue()           PORTDbits.RD3
#define UBT_SetDigitalInput()    do { TRISDbits.TRISD3 = 1; } while(0)
#define UBT_SetDigitalOutput()   do { TRISDbits.TRISD3 = 0; } while(0)
#define UBT_SetPullup()          do { WPUDbits.WPUD3 = 1; } while(0)
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#define RD6_SetHigh()            do { LATDbits.LATD6 = 1; } while(0)
#define RD6_SetLow()             do { LATDbits.LATD6 = 0; } while(0)
#define RD6_Toggle()             do { LATDbits.LATD6 = ~LATDbits.LATD6; } while(0)
#define RD6_GetValue()              PORTDbits.RD6
#define RD6_SetDigitalInput()    do { TRISDbits.TRISD6 = 1; } while(0)
#define RD6_SetDigitalOutput()   do { TRISDbits.TRISD6 = 0; } while(0)
#define RD6_SetPullup()             do { WPUDbits.WPUD6 = 1; } while(0)
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#define RD7_SetHigh()            do { LATDbits.LATD7 = 1; } while(0)
#define RD7_SetLow()             do { LATDbits.LATD7 = 0; } while(0)
#define RD7_Toggle()             do { LATDbits.LATD7 = ~LATDbits.LATD7; } while(0)
#define RD7_GetValue()              PORTDbits.RD7
#define RD7_SetDigitalInput()    do { TRISDbits.TRISD7 = 1; } while(0)
#define RD7_SetDigitalOutput()   do { TRISDbits.TRISD7 = 0; } while(0)
#define RD7_SetPullup()             do { WPUDbits.WPUD7 = 1; } while(0)
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   @Returns
    none
   @Description
    GPIO and peripheral I/O initialization
   @Example
    PIN_MANAGER_Initialize();
 */
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
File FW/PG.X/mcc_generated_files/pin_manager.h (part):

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*/
/**
  @Summary
    Sets the GPIO pin, RA0, high using LATA0.

  @Description
    Sets the GPIO pin, RA0, high using LATA0.

  @Preconditions
    The RA0 must be set to an output.
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#define RFU_A0_SetHigh()          ( LATASET = (1 << 0) )
/**
  @Summary
    Sets the GPIO pin, RA0, low using LATA0.

  @Description
    Sets the GPIO pin, RA0, low using LATA0.

  @Preconditions
    The RA0 must be set to an output.
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
/**
  @Summary
    Sets a value to the GPIO pin.

  @Description
    Sets or Resets the GPIO pin, RA0, low or high using LATA0.

  @Preconditions
    The RA0 must be set to an output.
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    None.

  @Param
    bool value; : value to be set to the GPIO pin.

  @Example
    <code>
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
/**
  @Summary
    Toggles the GPIO pin, RA0, using LATA0.

  @Description
    Toggles the GPIO pin, RA0, using LATA0.

  @Preconditions
    The RA0 must be set to an output.
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#define RFU_A0_Toggle()           ( LATAINV = (1 << 0) )
/**
  @Summary
    Reads the value of the GPIO pin, RA0.

  @Description
    Reads the value of the GPIO pin, RA0.

  @Preconditions
    None.
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    </code>

*/
#define RFU_A0_GetValue()         PORTAbits.RA0
/**
  @Summary
    Configures the GPIO pin, RA0, as an input.

  @Description
    Configures the GPIO pin, RA0, as an input.

  @Preconditions
    None.
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#define RFU_A0_SetDigitalInput()   ( TRISASET = (1 << 0) )
/**
  @Summary
    Configures the GPIO pin, RA0, as an output.

  @Description
    Configures the GPIO pin, RA0, as an output.

  @Preconditions
    None.
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#define RFU_A0_SetDigitalOutput()   ( TRISACLR = (1 << 0) )
/**
  @Summary
    Sets the GPIO pin, RA1, high using LATA1.

  @Description
    Sets the GPIO pin, RA1, high using LATA1.

  @Preconditions
    The RA1 must be set to an output.
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#define RFU_A1_SetHigh()          ( LATASET = (1 << 1) )
/**
  @Summary
    Sets the GPIO pin, RA1, low using LATA1.

  @Description
    Sets the GPIO pin, RA1, low using LATA1.

  @Preconditions
    The RA1 must be set to an output.
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
/**
  @Summary
    Sets a value to the GPIO pin.

  @Description
    Sets or Resets the GPIO pin, RA1, low or high using LATA1.

  @Preconditions
    The RA1 must be set to an output.
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    None.

  @Param
    bool value; : value to be set to the GPIO pin.

  @Example
    <code>
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
/**
  @Summary
    Toggles the GPIO pin, RA1, using LATA1.

  @Description
    Toggles the GPIO pin, RA1, using LATA1.

  @Preconditions
    The RA1 must be set to an output.
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#define RFU_A1_Toggle()           ( LATAINV = (1 << 1) )
/**
  @Summary
    Reads the value of the GPIO pin, RA1.

  @Description
    Reads the value of the GPIO pin, RA1.

  @Preconditions
    None.
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    </code>

*/
#define RFU_A1_GetValue()         PORTAbits.RA1
/**
  @Summary
    Configures the GPIO pin, RA1, as an input.

  @Description
    Configures the GPIO pin, RA1, as an input.

  @Preconditions
    None.
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#define RFU_A1_SetDigitalInput()   ( TRISASET = (1 << 1) )
/**
  @Summary
    Configures the GPIO pin, RA1, as an output.

  @Description
    Configures the GPIO pin, RA1, as an output.

  @Preconditions
    None.
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#define RFU_A1_SetDigitalOutput()   ( TRISACLR = (1 << 1) )
/**
  @Summary
    Sets the GPIO pin, RA4, high using LATA4.

  @Description
    Sets the GPIO pin, RA4, high using LATA4.

  @Preconditions
    The RA4 must be set to an output.
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#define BOOT_N_SetHigh()          ( LATASET = (1 << 4) )
/**
  @Summary
    Sets the GPIO pin, RA4, low using LATA4.

  @Description
    Sets the GPIO pin, RA4, low using LATA4.

  @Preconditions
    The RA4 must be set to an output.
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
/**
  @Summary
    Sets a value to the GPIO pin.

  @Description
    Sets or Resets the GPIO pin, RA4, low or high using LATA4.

  @Preconditions
    The RA4 must be set to an output.
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    None.

  @Param
    bool value; : value to be set to the GPIO pin.

  @Example
    <code>
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
/**
  @Summary
    Toggles the GPIO pin, RA4, using LATA4.

  @Description
    Toggles the GPIO pin, RA4, using LATA4.

  @Preconditions
    The RA4 must be set to an output.
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#define BOOT_N_Toggle()           ( LATAINV = (1 << 4) )
/**
  @Summary
    Reads the value of the GPIO pin, RA4.

  @Description
    Reads the value of the GPIO pin, RA4.

  @Preconditions
    None.
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    </code>

*/
#define BOOT_N_GetValue()         PORTAbits.RA4
/**
  @Summary
    Configures the GPIO pin, RA4, as an input.

  @Description
    Configures the GPIO pin, RA4, as an input.

  @Preconditions
    None.
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#define BOOT_N_SetDigitalInput()   ( TRISASET = (1 << 4) )
/**
  @Summary
    Configures the GPIO pin, RA4, as an output.

  @Description
    Configures the GPIO pin, RA4, as an output.

  @Preconditions
    None.
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#define BOOT_N_SetDigitalOutput()   ( TRISACLR = (1 << 4) )
/**
  @Summary
    Sets the GPIO pin, RB0, high using LATB0.

  @Description
    Sets the GPIO pin, RB0, high using LATB0.

  @Preconditions
    The RB0 must be set to an output.
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#define PG_PGD_SetHigh()          ( LATBSET = (1 << 0) )
/**
  @Summary
    Sets the GPIO pin, RB0, low using LATB0.

  @Description
    Sets the GPIO pin, RB0, low using LATB0.

  @Preconditions
    The RB0 must be set to an output.
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
/**
  @Summary
    Sets a value to the GPIO pin.

  @Description
    Sets or Resets the GPIO pin, RB0, low or high using LATB0.

  @Preconditions
    The RB0 must be set to an output.
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    None.

  @Param
    bool value; : value to be set to the GPIO pin.

  @Example
    <code>
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
/**
  @Summary
    Toggles the GPIO pin, RB0, using LATB0.

  @Description
    Toggles the GPIO pin, RB0, using LATB0.

  @Preconditions
    The RB0 must be set to an output.
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#define PG_PGD_Toggle()           ( LATBINV = (1 << 0) )
/**
  @Summary
    Reads the value of the GPIO pin, RB0.

  @Description
    Reads the value of the GPIO pin, RB0.

  @Preconditions
    None.
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    </code>

*/
#define PG_PGD_GetValue()         PORTBbits.RB0
/**
  @Summary
    Configures the GPIO pin, RB0, as an input.

  @Description
    Configures the GPIO pin, RB0, as an input.

  @Preconditions
    None.
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#define PG_PGD_SetDigitalInput()   ( TRISBSET = (1 << 0) )
/**
  @Summary
    Configures the GPIO pin, RB0, as an output.

  @Description
    Configures the GPIO pin, RB0, as an output.

  @Preconditions
    None.
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#define PG_PGD_SetDigitalOutput()   ( TRISBCLR = (1 << 0) )
/**
  @Summary
    Sets the GPIO pin, RB1, high using LATB1.

  @Description
    Sets the GPIO pin, RB1, high using LATB1.

  @Preconditions
    The RB1 must be set to an output.
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#define PG_PGC_SetHigh()          ( LATBSET = (1 << 1) )
/**
  @Summary
    Sets the GPIO pin, RB1, low using LATB1.

  @Description
    Sets the GPIO pin, RB1, low using LATB1.

  @Preconditions
    The RB1 must be set to an output.
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
/**
  @Summary
    Sets a value to the GPIO pin.

  @Description
    Sets or Resets the GPIO pin, RB1, low or high using LATB1.

  @Preconditions
    The RB1 must be set to an output.
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    None.

  @Param
    bool value; : value to be set to the GPIO pin.

  @Example
    <code>
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
/**
  @Summary
    Toggles the GPIO pin, RB1, using LATB1.

  @Description
    Toggles the GPIO pin, RB1, using LATB1.

  @Preconditions
    The RB1 must be set to an output.
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#define PG_PGC_Toggle()           ( LATBINV = (1 << 1) )
/**
  @Summary
    Reads the value of the GPIO pin, RB1.

  @Description
    Reads the value of the GPIO pin, RB1.

  @Preconditions
    None.
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    </code>

*/
#define PG_PGC_GetValue()         PORTBbits.RB1
/**
  @Summary
    Configures the GPIO pin, RB1, as an input.

  @Description
    Configures the GPIO pin, RB1, as an input.

  @Preconditions
    None.
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#define PG_PGC_SetDigitalInput()   ( TRISBSET = (1 << 1) )
/**
  @Summary
    Configures the GPIO pin, RB1, as an output.

  @Description
    Configures the GPIO pin, RB1, as an output.

  @Preconditions
    None.
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#define PG_PGC_SetDigitalOutput()   ( TRISBCLR = (1 << 1) )
/**
  @Summary
    Sets the GPIO pin, RB13, high using LATB13.

  @Description
    Sets the GPIO pin, RB13, high using LATB13.

  @Preconditions
    The RB13 must be set to an output.
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#define RLED_EXT_SetHigh()          ( LATBSET = (1 << 13) )
/**
  @Summary
    Sets the GPIO pin, RB13, low using LATB13.

  @Description
    Sets the GPIO pin, RB13, low using LATB13.

  @Preconditions
    The RB13 must be set to an output.
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
/**
  @Summary
    Sets a value to the GPIO pin.

  @Description
    Sets or Resets the GPIO pin, RB13, low or high using LATB13.

  @Preconditions
    The RB13 must be set to an output.
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    None.

  @Param
    bool value; : value to be set to the GPIO pin.

  @Example
    <code>
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
/**
  @Summary
    Toggles the GPIO pin, RB13, using LATB13.

  @Description
    Toggles the GPIO pin, RB13, using LATB13.

  @Preconditions
    The RB13 must be set to an output.
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#define RLED_EXT_Toggle()           ( LATBINV = (1 << 13) )
/**
  @Summary
    Reads the value of the GPIO pin, RB13.

  @Description
    Reads the value of the GPIO pin, RB13.

  @Preconditions
    None.
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#define RLED_EXT_GetValue()         PORTBbits.RB13
/**
  @Summary
    Configures the GPIO pin, RB13, as an input.
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

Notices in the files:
FW/PG.X/mcc_generated_files/pin_manager.h:
(c) 2020 Microchip Technology Inc. and its subsidiaries. You may use this
FW/TG.X/mcc_generated_files/pin_manager.h:
(c) 2018 Microchip Technology Inc. and its subsidiaries.
